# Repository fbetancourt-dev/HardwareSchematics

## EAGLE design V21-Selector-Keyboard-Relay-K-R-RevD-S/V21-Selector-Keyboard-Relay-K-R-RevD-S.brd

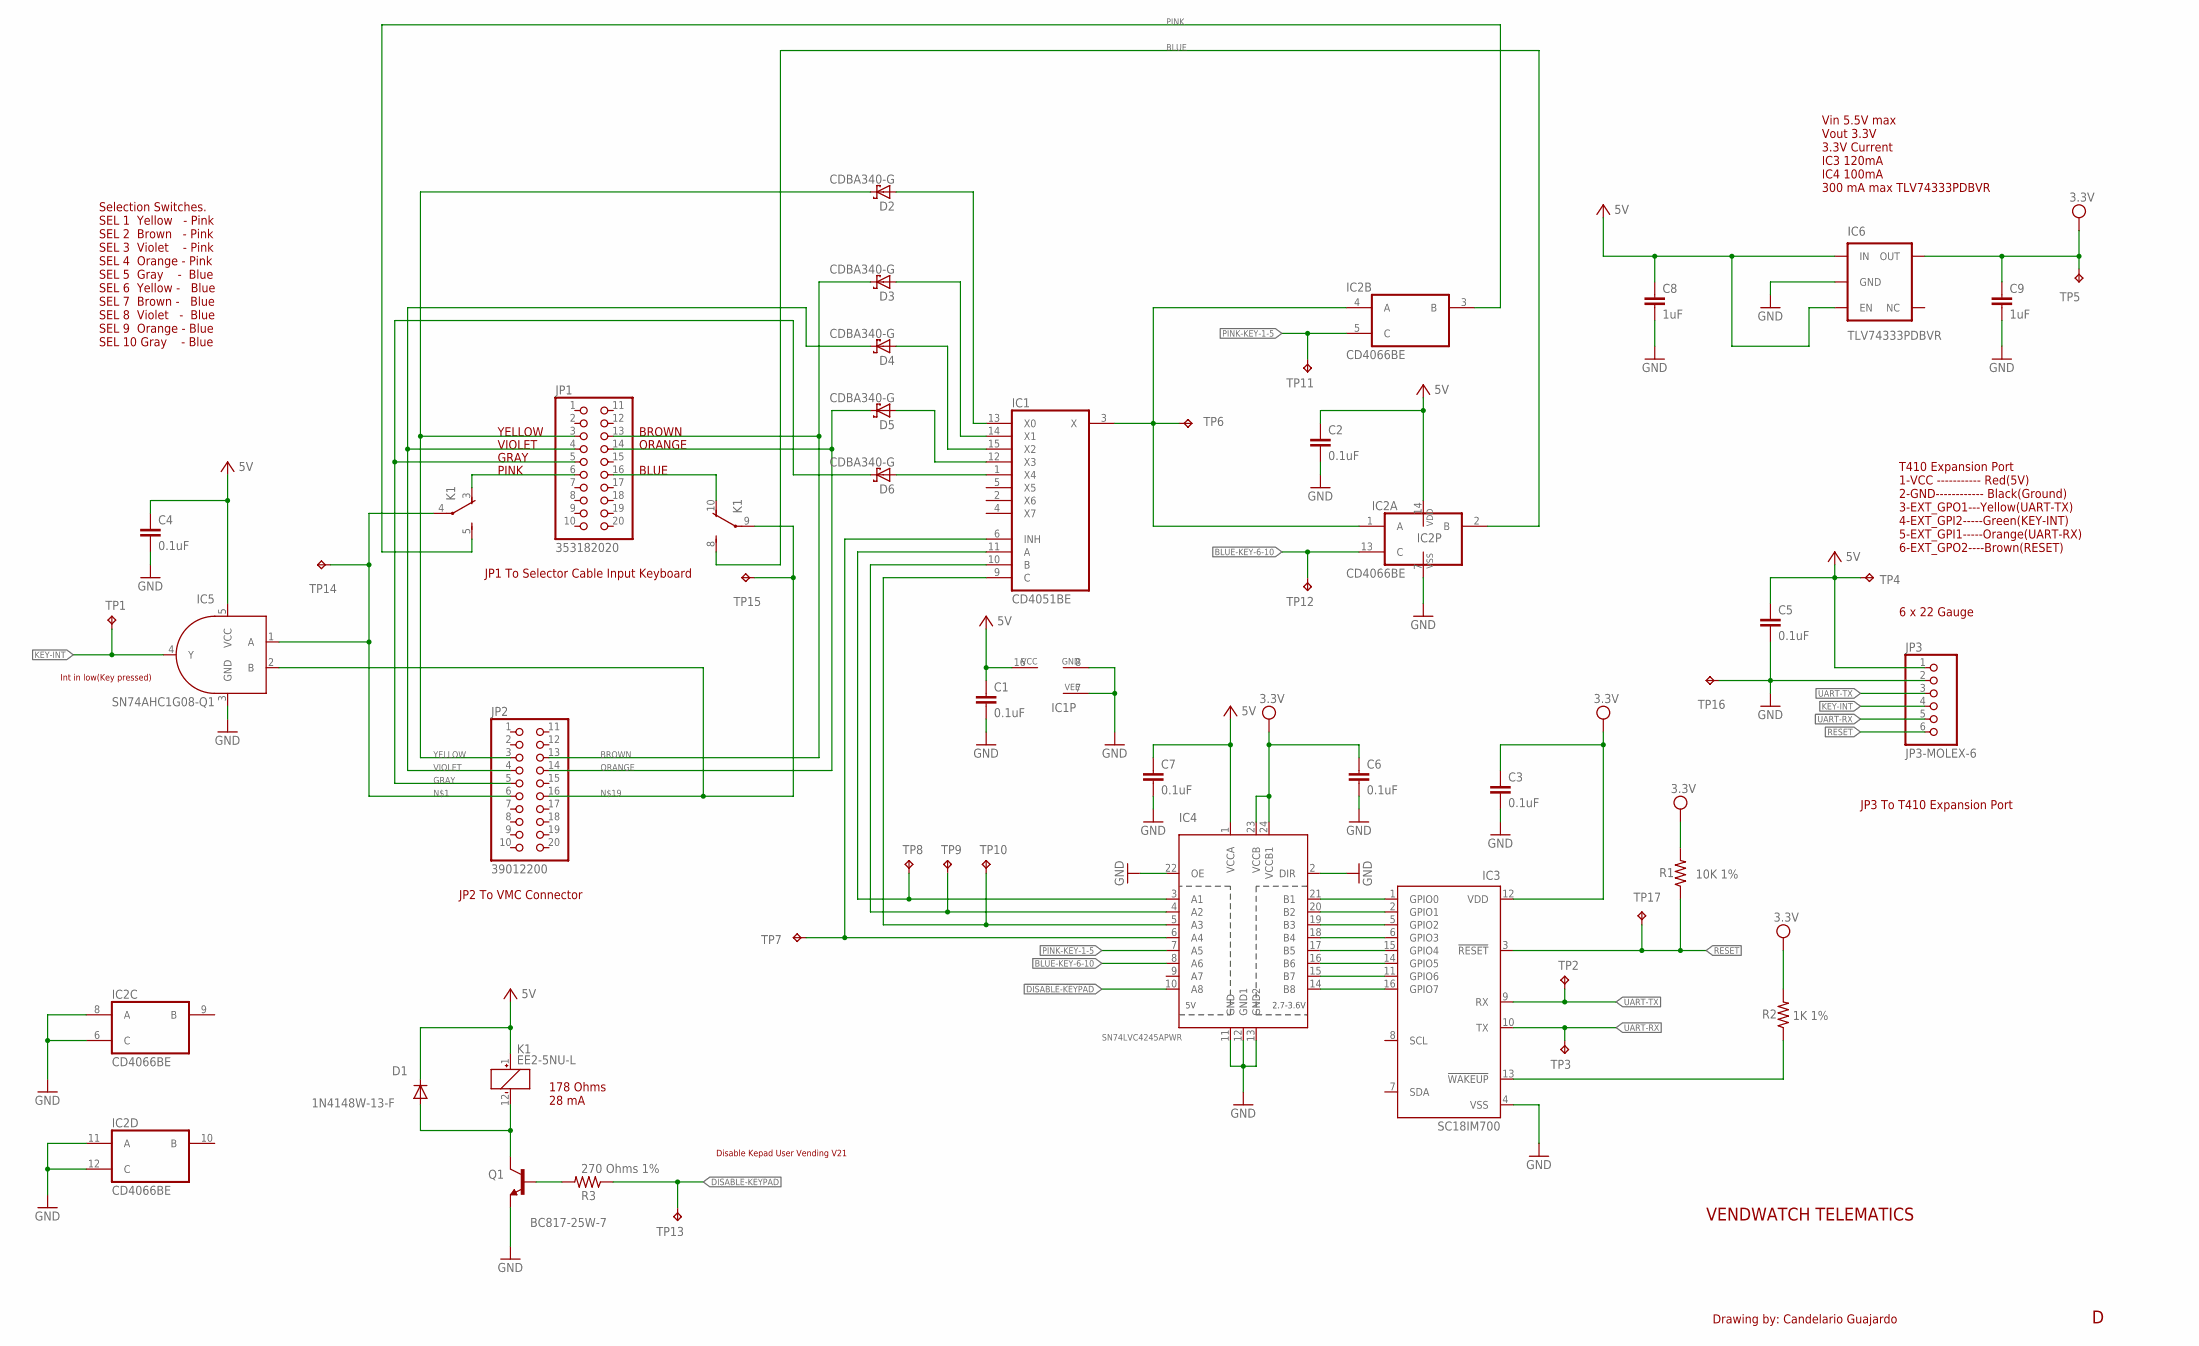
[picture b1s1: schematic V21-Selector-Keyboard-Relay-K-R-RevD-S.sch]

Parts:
C1, C2, C3, C4, C5, C6, C7: 0.1uF; 0805
C8, C9: 1uF; 0805
D1: 1N4148W-13-F; SOD-123
D2, D3, D4, D5, D6: CDBA340-G; DO-214AC-SMA
IC1: CD4051BE; SO16
IC2: CD4066BE; SO14
IC3: SC18IM700; TSSOP16; MPN SC18IM700IPW/S8HP
IC4: SN74LVC4245APWR; SOIC24
IC5: SN74AHC1G08-Q1; SOT23-5
IC6: TLV74333PDBVR; SOT-23-5
JP1: 353182020; 2X10-4.2MM-TH-RA
JP2: 39012200; 2X10-4.2MM-FS-CRIMP
JP3: JP3-MOLEX-6; HEADER-1X6-22-GAUGE-OVAL
K1: EE2-5NU-L; DPDT-2-FROM-C-EE2
Q1: BC817-25W-7; SOT323
R1: 10K 1%; 0805
R2: 1K 1%; 0805
R3: 270 Ohms 1%; 0805
TP1, TP2, TP3, TP4, TP5, TP6, TP7, TP8, TP9, TP10, TP11, TP12, TP13, TP14, TP15, TP16, TP17: TPB1,27; B1,27

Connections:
3.3V: C3.1, C6.1, C9.1, IC3.12 (VDD), IC4.23 (VCCB), IC4.24 (VCCB1), IC6.5 (OUT), R1.2, R2.2, TP5.TP
5V: C1.1, C2.1, C4.1, C5.1, C7.1, C8.1, D1.C, IC1.16 (VCC), IC2.14 (VDD), IC4.1 (VCCA), IC5.5 (VCC), IC6.1 (IN), IC6.3 (EN), JP3.1, K1.1 (+), TP4.TP
BLUE: IC2.2 (B), K1.8 (S)
BLUE-KEY-6-10: IC2.13 (C), IC4.8 (A6), TP12.TP
BROWN: D3.K (C), JP1.13, JP2.13
DISABLE-KEYPAD: IC4.10 (A8), R3.1, TP13.TP
GND: C1.2, C2.2, C3.2, C4.2, C5.2, C6.2, C7.2, C8.2, C9.2, IC1.7 (VEE), IC1.8 (GND), IC2.6 (C), IC2.7 (VSS), IC2.8 (A), IC2.11 (A), IC2.12 (C), IC3.4 (VSS), IC4.2 (DIR), IC4.11 (GND), IC4.12 (GND1), IC4.13 (GND2), IC4.22 (OE), IC5.3 (GND), IC6.2 (GND), JP3.2, Q1.2 (E), TP16.TP
GRAY: D6.K (C), JP1.5, JP2.5
KEY-INT: IC5.4 (Y), JP3.4, TP1.TP
unnamed: IC5.1 (A), JP2.6, K1.4, TP14.TP
unnamed: JP1.6, K1.3 (O)
unnamed: JP1.16, K1.10 (O)
unnamed: IC3.13 (!WAKEUP), R2.1
unnamed: IC3.1 (GPIO0), IC4.21 (B1)
unnamed: IC3.2 (GPIO1), IC4.20 (B2)
unnamed: IC1.6 (INH), IC4.6 (A4), TP7.TP
unnamed: IC1.3 (X), IC2.1 (A), IC2.4 (A), TP6.TP
unnamed: IC3.5 (GPIO2), IC4.19 (B3)
unnamed: IC3.6 (GPIO3), IC4.18 (B4)
unnamed: IC1.11 (A), IC4.3 (A1), TP8.TP
unnamed: IC1.10 (B), IC4.4 (A2), TP9.TP
unnamed: IC1.9 (C), IC4.5 (A3), TP10.TP
unnamed: IC3.15 (GPIO4), IC4.17 (B5)
unnamed: IC3.14 (GPIO5), IC4.16 (B6)
unnamed: IC3.11 (GPIO6), IC4.15 (B7)
unnamed: IC3.16 (GPIO7), IC4.14 (B8)
unnamed: IC5.2 (B), JP2.16, K1.9, TP15.TP
unnamed: D1.A, K1.12 (-), Q1.3 (C)
unnamed: D2.A, IC1.13 (X0)
unnamed: Q1.1 (B), R3.2
unnamed: D3.A, IC1.14 (X1)
unnamed: D4.A, IC1.15 (X2)
unnamed: D5.A, IC1.12 (X3)
unnamed: D6.A, IC1.1 (X4)
ORANGE: D5.K (C), JP1.14, JP2.14
PINK: IC2.3 (B), K1.5 (S)
PINK-KEY-1-5: IC2.5 (C), IC4.7 (A5), TP11.TP
RESET: IC3.3 (!RESET), JP3.6, R1.1, TP17.TP
UART-RX: IC3.10 (TX), JP3.5, TP3.TP
UART-TX: IC3.9 (RX), JP3.3, TP2.TP
VIOLET: D4.K (C), JP1.4, JP2.4
YELLOW: D2.K (C), JP1.3, JP2.3

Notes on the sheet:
VENDWATCH TELEMATICS
Drawing by: Candelario Guajardo
BLUE
BROWN
ORANGE
GRAY
YELLOW
VIOLET
PINK
Int in low(Key pressed)
T410 Expansion Port 1-VCC ----------- Red(5V) 2-GND------------ Black(Ground) 3-EXT_GPO1---Yellow(UART-TX) 4-EXT_GPI2-----Green(KEY-INT) 5-EXT_GPI1-----Orange(UART-RX) 6-EXT_GPO2----Brown(RESET)
Selection Switches. SEL 1 Yellow - Pink SEL 2 Brown - Pink SEL 3 Violet - Pink SEL 4 Orange - Pink SEL 5 Gray - Blue SEL 6 Yellow - Blue SEL 7 Brown - Blue SEL 8 Violet - Blue SEL 9 Orange - Blue SEL 10 Gray - Blue
JP2 To VMC Connector
JP1 To Selector Cable Input Keyboard
JP3 To T410 Expansion Port
Disable Kepad User Vending V21
Vin 5.5V max Vout 3.3V 3.3V Current IC3 120mA IC4 100mA 300 mA max TLV74333PDBVR
6 x 22 Gauge
178 Ohms 28 mA

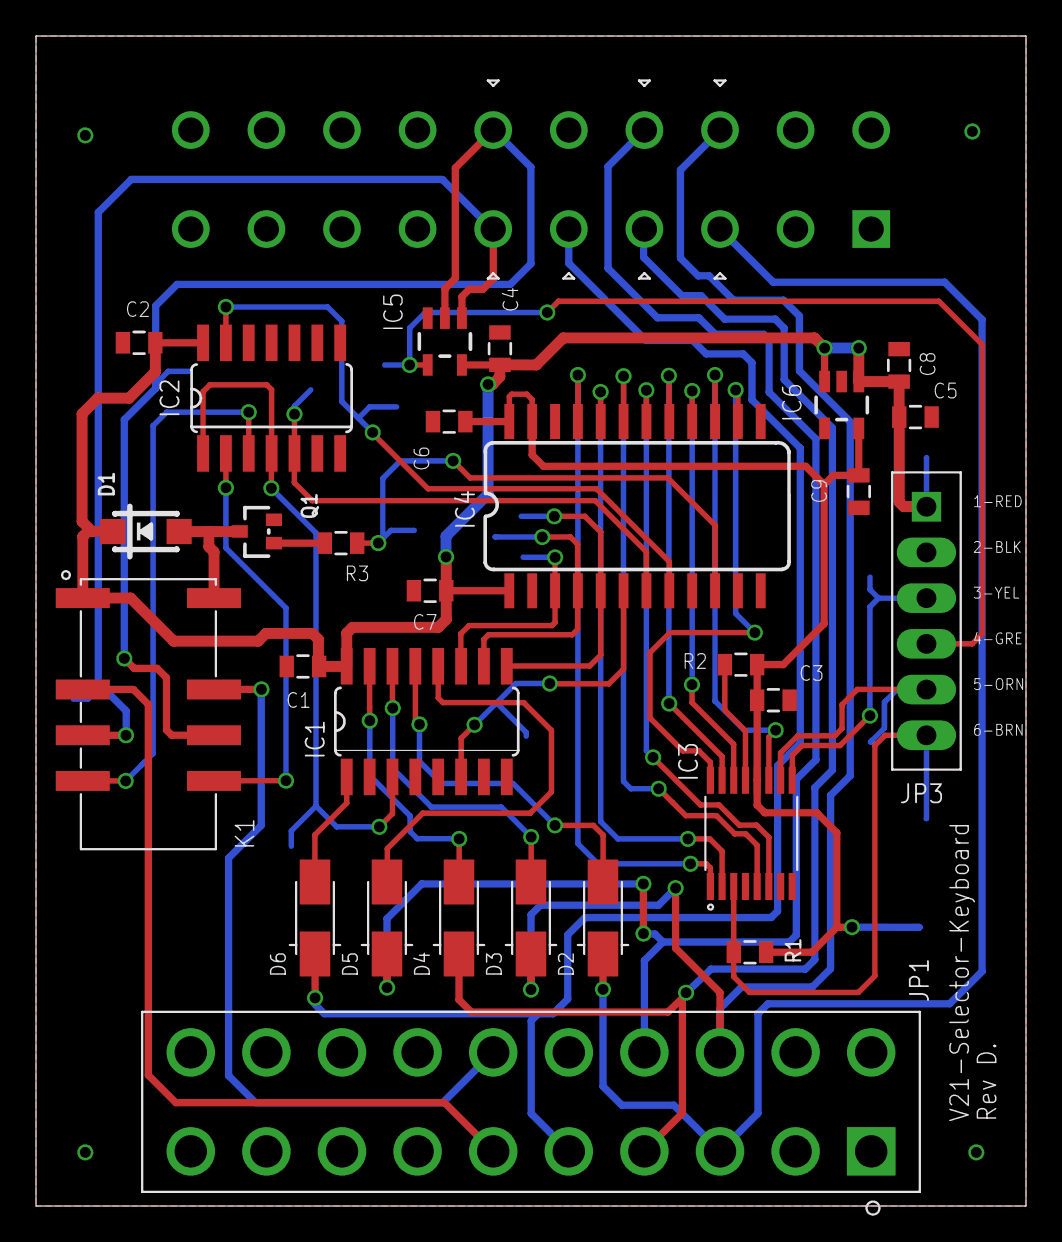
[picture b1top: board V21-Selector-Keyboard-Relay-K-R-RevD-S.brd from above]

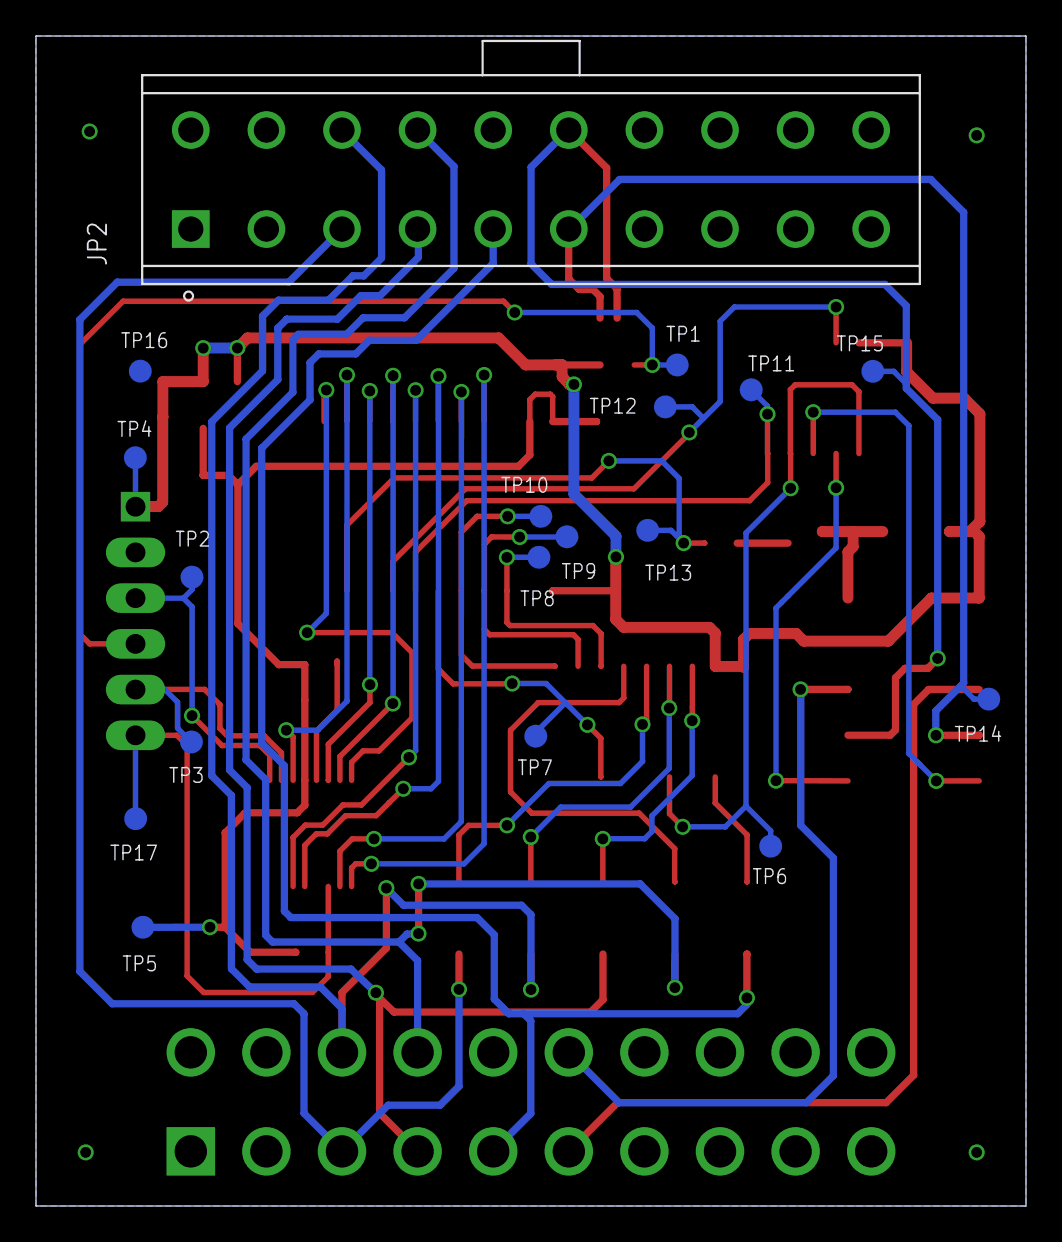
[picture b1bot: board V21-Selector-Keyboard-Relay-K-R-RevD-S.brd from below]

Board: 2 copper layers, 55.0 x 65.0 mm, 46 parts (18 on the bottom side), 42 nets.

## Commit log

2020-10-15 Added V21-Selector-Keyboard-Relay-K-R-RevD-S

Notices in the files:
parts and their libraries:
SparkFun-Capacitors: Licensing: CC v3.0 Share-Alike You are welcome to use this library for commercial purposes.
microbuilder: This work is placed in the public domain, and may be freely used for commercial and non-commercial work with the following conditions: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
